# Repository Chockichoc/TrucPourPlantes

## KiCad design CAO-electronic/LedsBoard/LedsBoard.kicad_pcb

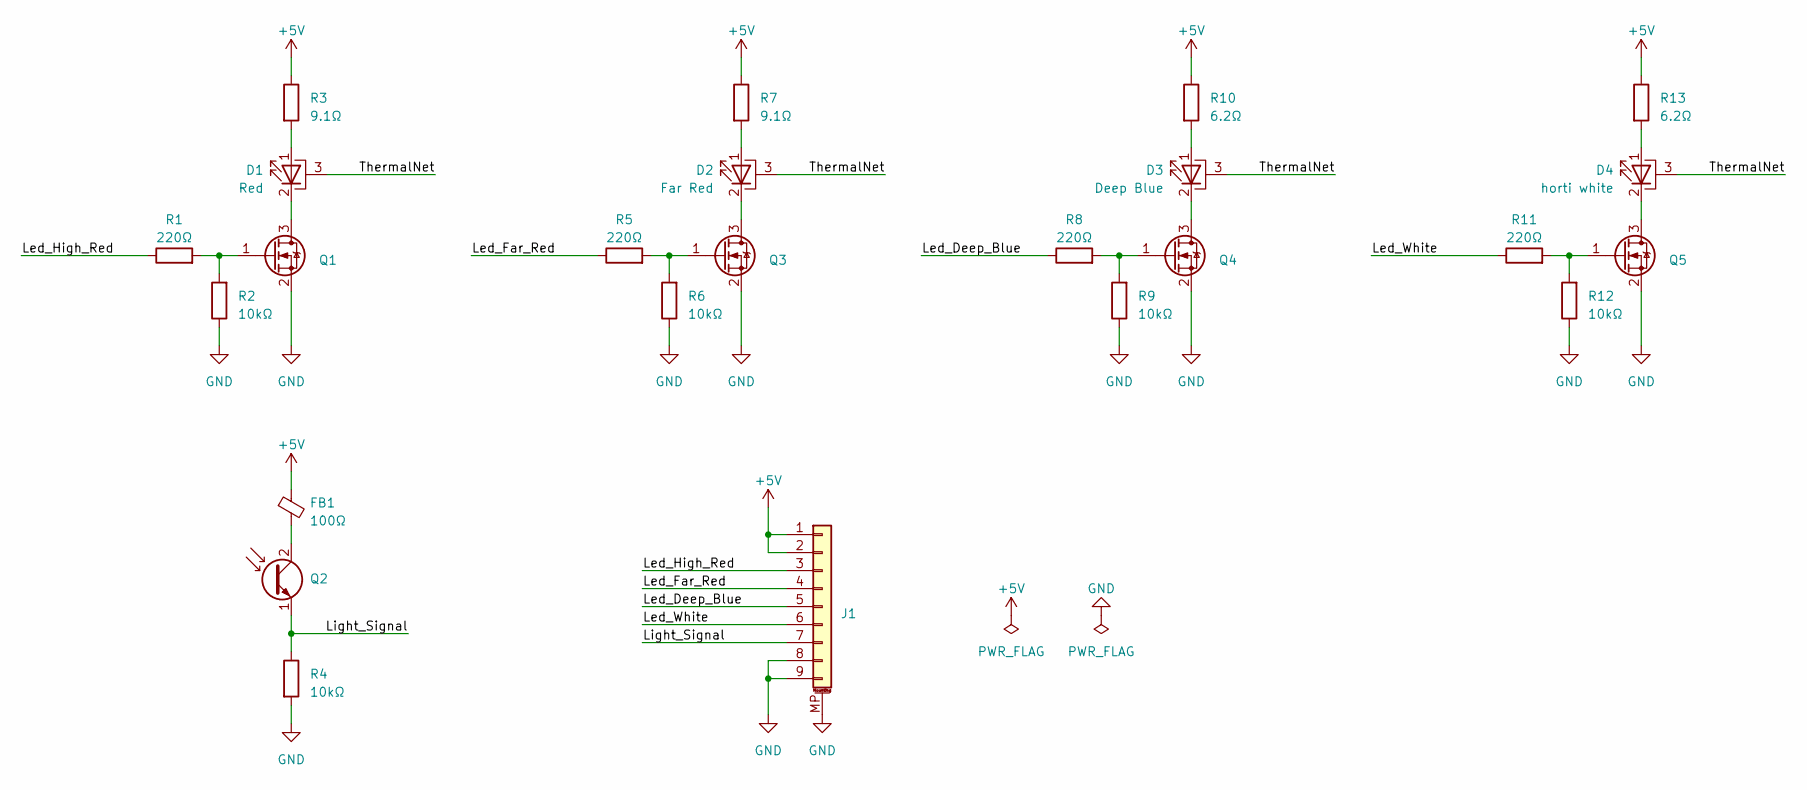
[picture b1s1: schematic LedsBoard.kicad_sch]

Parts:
D1: Red; LED_Osram_GH_CSSRML.24
D2: Far Red; LED_Osram_GF_CSSRML.24
D3: Deep Blue; LED_Osram_GD_CSSRML.14-U9V2-24-1
D4: horti white; LED_Osram_GW_CSSRML.HW
FB1: 100Ω; L_0603_1608Metric
J1: Würth_WR-WTB_620109131822_1x09_P2.00mm_Horizontal
Q1, Q3, Q4, Q5: SOT-323_SC-70
Q2: Sensor_Light_Vishay_TEMT6000
R1, R5, R8, R11: 220Ω; R_0402_1005Metric
R2, R4, R6, R9, R12: 10kΩ; R_0402_1005Metric
R3, R7: 9.1Ω; R_1225(reversed)
R10, R13: 6.2Ω; R_1225(reversed)

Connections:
+5V: FB1.1, J1.1, J1.2, R3.1, R7.1, R10.1, R13.1
/Led_Deep_Blue: J1.5, R8.1
/Led_Far_Red: J1.4, R5.1
/Led_High_Red: J1.3, R1.1
/Led_White: J1.6, R11.1
/Light_Signal: J1.7, Q2.1 (E), R4.1
/ThermalNet: D1.3 (PAD), D2.3 (PAD), D3.3 (PAD), D4.3 (PAD)
GND: J1.8, J1.9, J1.MP (MountPin), Q1.2 (S), Q3.2 (S), Q4.2 (S), Q5.2 (S), R2.1, R4.2, R6.1, R9.1, R12.1
unnamed: D1.1 (A), R3.2
unnamed: D1.2 (K), Q1.3 (D)
unnamed: D2.1 (A), R7.2
unnamed: D2.2 (K), Q3.3 (D)
unnamed: D3.1 (A), R10.2
unnamed: D3.2 (K), Q4.3 (D)
unnamed: D4.1 (A), R13.2
unnamed: D4.2 (K), Q5.3 (D)
unnamed: Q1.1 (G), R1.2, R2.2
unnamed: FB1.2, Q2.2 (C)
unnamed: Q3.1 (G), R5.2, R6.2
unnamed: Q4.1 (G), R8.2, R9.2
unnamed: Q5.1 (G), R11.2, R12.2

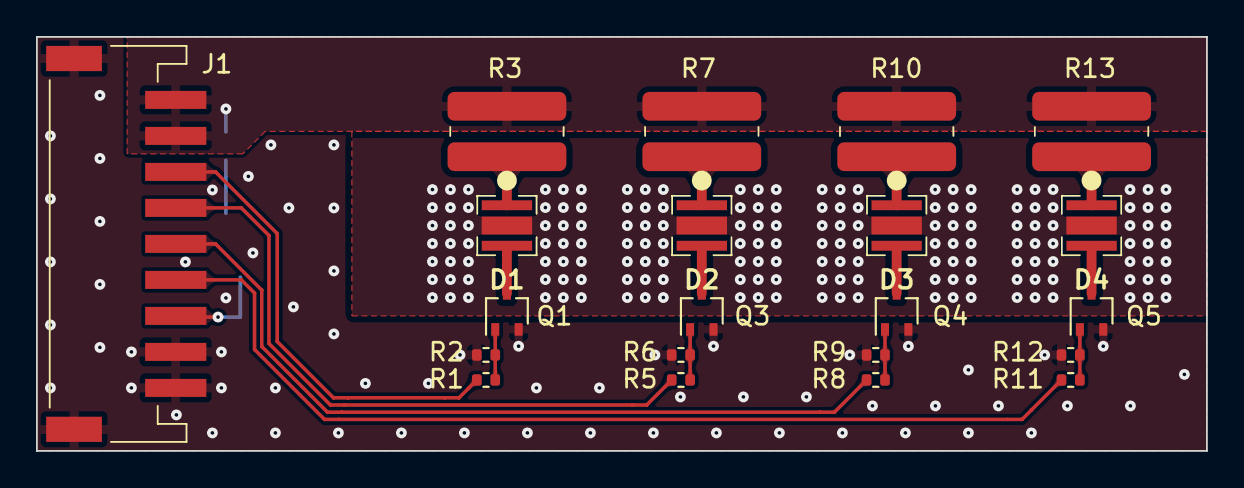
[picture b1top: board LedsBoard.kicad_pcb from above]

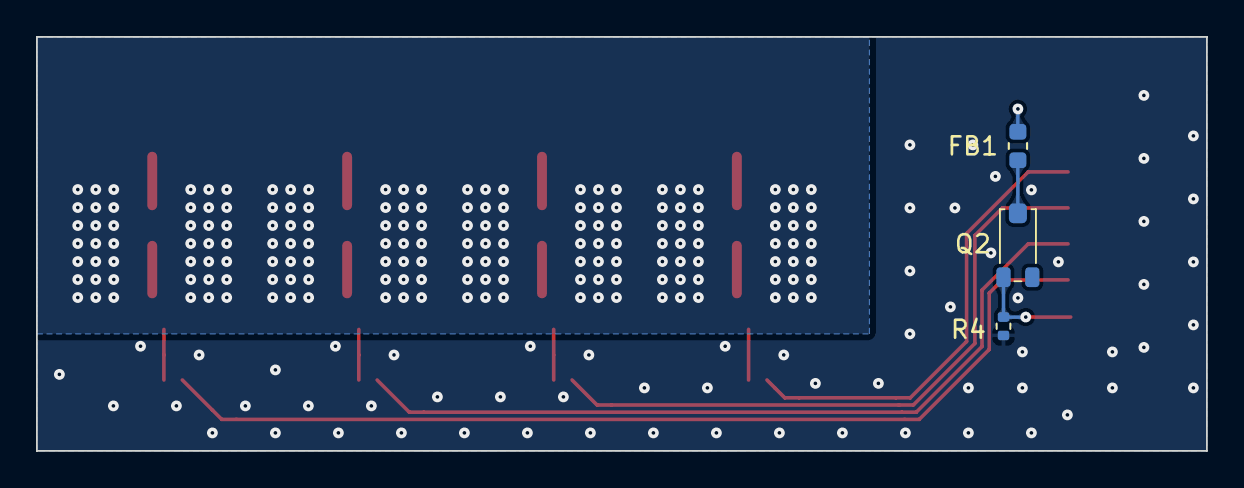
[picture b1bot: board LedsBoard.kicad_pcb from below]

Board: 2 copper layers, 65.0 x 23.0 mm, 24 parts (3 on the bottom side), 21 nets.

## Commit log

2023-03-20 Create LICENCE
2023-03-20 Update LICENCE
2023-03-20 update project filepaths
2023-03-20 update project with gitignore setting
2023-03-20 first proto
